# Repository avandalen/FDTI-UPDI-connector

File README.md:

# Small ATtiny self-clamping program connector
See the full article: https://www.avdweb.nl/arduino/attiny3217/ftdi-updi-connector
Typically, debugging via the serial monitor and burning the bootloader requires 2 connectors:  FTDI and UPDI (like the ICSP connector for the Atmega328 and others) These connectors, however, take up a lot of space on the pcb, especially with respect to the fact that the ATtiny devices, such as the ATtiny3217, are very small. That is why I have designed a new combined FTDI / UPDI connector, which take less space on the pcb.

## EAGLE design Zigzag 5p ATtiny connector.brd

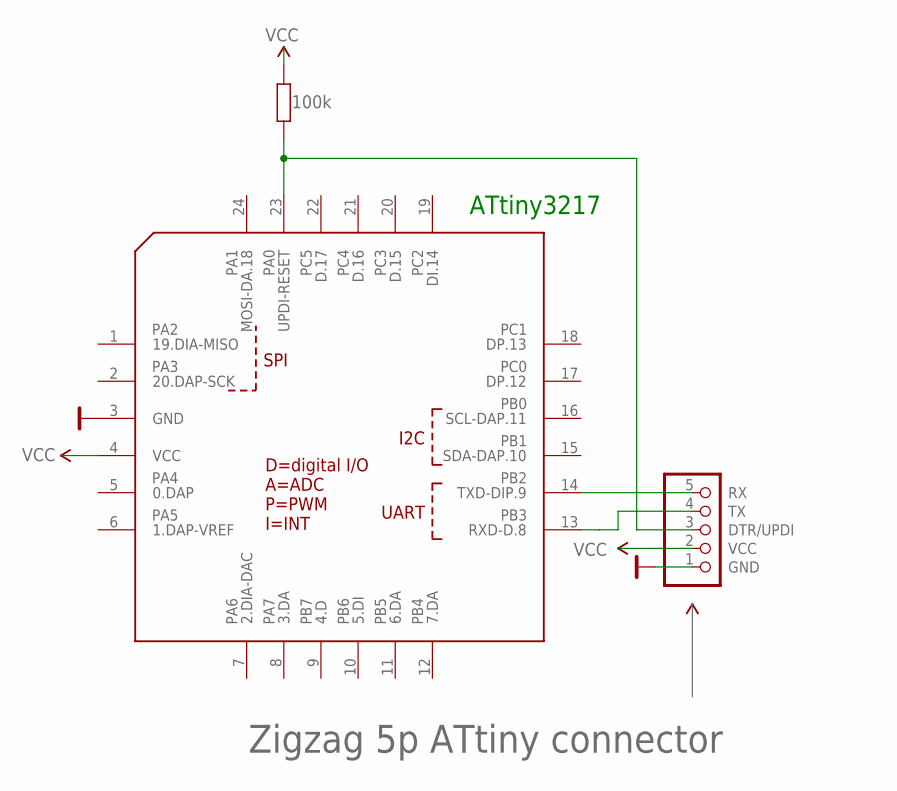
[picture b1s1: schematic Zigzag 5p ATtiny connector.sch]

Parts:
J1: 5 pin 0.05" ZIGZAG connector; ZIGZAG-FTDI-UPDI-5P
R1: 100k; 0603
U2: ATtiny3217; QFN-24

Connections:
DTR/UPDI: J1.3 (DTR/UPDI), R1.1, U2.23 (UPDI-RESET)
GND: J1.1 (GND), U2.3 (GND)
unnamed: J1.5 (RX), U2.14 (TXD-DIP.9)
unnamed: J1.4 (TX), U2.13 (RXD-D.8)
VCC: J1.2 (VCC), R1.2, U2.4 (VCC)

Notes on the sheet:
Zigzag 5p ATtiny connector
ATtiny3217

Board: 2 copper layers, 3 parts (0 on the bottom side), 5 nets, no tracks yet.

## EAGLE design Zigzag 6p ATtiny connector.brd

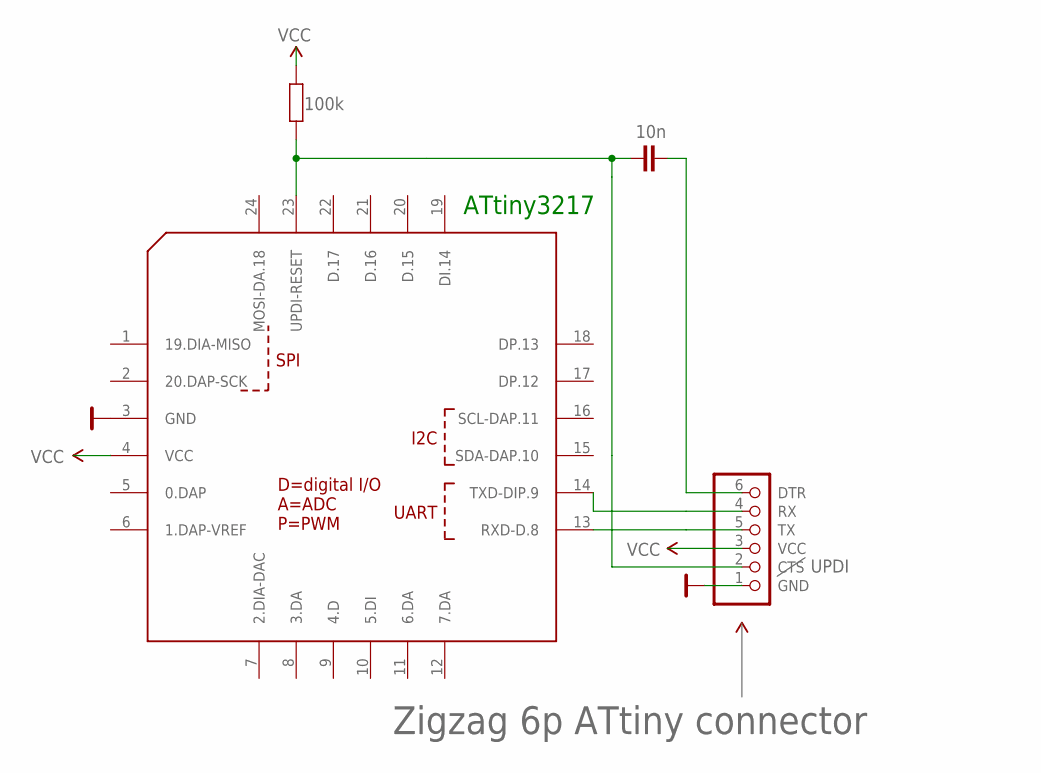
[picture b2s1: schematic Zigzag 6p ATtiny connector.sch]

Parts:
C2: 10n; 0603-SMALL
J2: FTDI; ZIGZAG-FTDI
R2: 100k; 0603-SMALL
U1: ATTINY3217-; QFN-24

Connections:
GND: J2.1 (GND), U1.3 (GND)
unnamed: C2.2, J2.6 (DTR)
unnamed: J2.4 (RX), U1.14 (TXD-DIP.9)
unnamed: J2.5 (TX), U1.13 (RXD-D.8)
UPDI: C2.1, J2.2 (CTS), R2.1, U1.23 (UPDI-RESET)
VCC: J2.3 (VCC), R2.2, U1.4 (VCC)

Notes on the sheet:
Zigzag 6p ATtiny connector
ATtiny3217

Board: 2 copper layers, 4 parts (0 on the bottom side), 6 nets, no tracks yet.

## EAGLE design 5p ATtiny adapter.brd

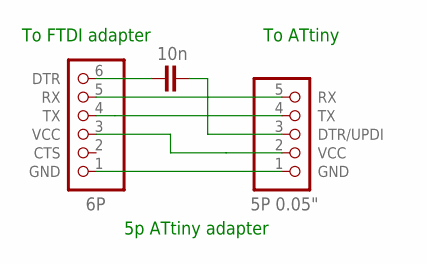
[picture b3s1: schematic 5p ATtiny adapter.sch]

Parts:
C1: 10n; 0603-SMALL
J1: 6P; 1X06
J2: 5P 0.05"; FTDI-UPDI-5P

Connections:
5V: J1.3 (VCC), J2.2 (VCC)
GND: J1.1 (GND), J2.1 (GND)
unnamed: C1.2, J2.3 (DTR/UPDI)
unnamed: C1.1, J1.6 (DTR)
unnamed: J1.5 (RX), J2.5 (RX)
unnamed: J1.4 (TX), J2.4 (TX)

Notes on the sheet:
5p ATtiny adapter
To FTDI adapter
To ATtiny

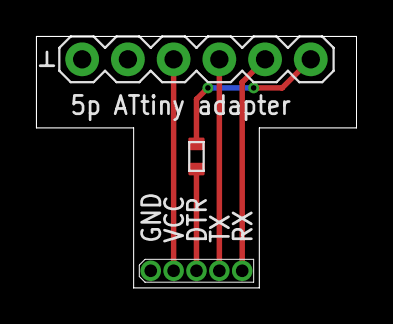
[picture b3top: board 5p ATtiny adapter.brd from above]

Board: 2 copper layers, 17.8 x 14.0 mm, 3 parts (0 on the bottom side), 6 nets.

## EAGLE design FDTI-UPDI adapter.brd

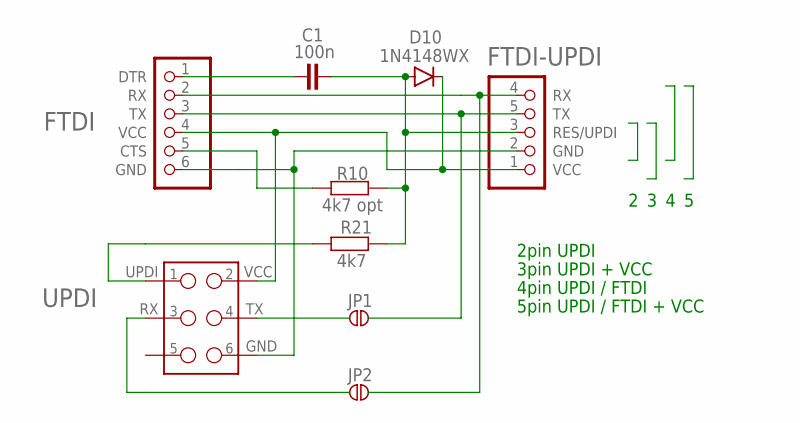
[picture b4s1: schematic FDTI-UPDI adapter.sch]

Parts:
C1: 100n; 0603-SMALL
D10: 1N4148WX; SOD-323
J2: FTDI; ZIGZAG-FTDI
J100: FTDI-UPDI; FTDI-UPDI-ZIGZAG
JP1, JP2: JUMPER_SJSMALL; SJ_2S-NO-NS
R10: 4k7 opt; 0603-SMALL
R21: 4k7; 0603-SMALL
UPDI: M3X2"; 2X3_TEST_POINTS

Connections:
4555: C1.2, D10.A, J100.3 (RES/UPDI), R10.1, R21.1
DTR1: C1.1, J2.1 (DTR)
GND: J2.6 (GND), J100.2 (GND), UPDI.6
unnamed: J2.5 (CTS), R10.2
RX: JP2.2, UPDI.3
RX1: J2.2 (RX), J100.4 (RX), JP2.1
TX: JP1.2, UPDI.4
TX1: J2.3 (TX), J100.5 (TX), JP1.1
UPDI: R21.2, UPDI.1
VCC: D10.C, J2.4 (VCC), J100.1 (VCC), UPDI.2

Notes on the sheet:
2pin UPDI
3pin UPDI + VCC
4pin UPDI / FTDI
5pin UPDI / FTDI + VCC

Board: 2 copper layers, 9 parts (0 on the bottom side), 10 nets, no tracks yet.

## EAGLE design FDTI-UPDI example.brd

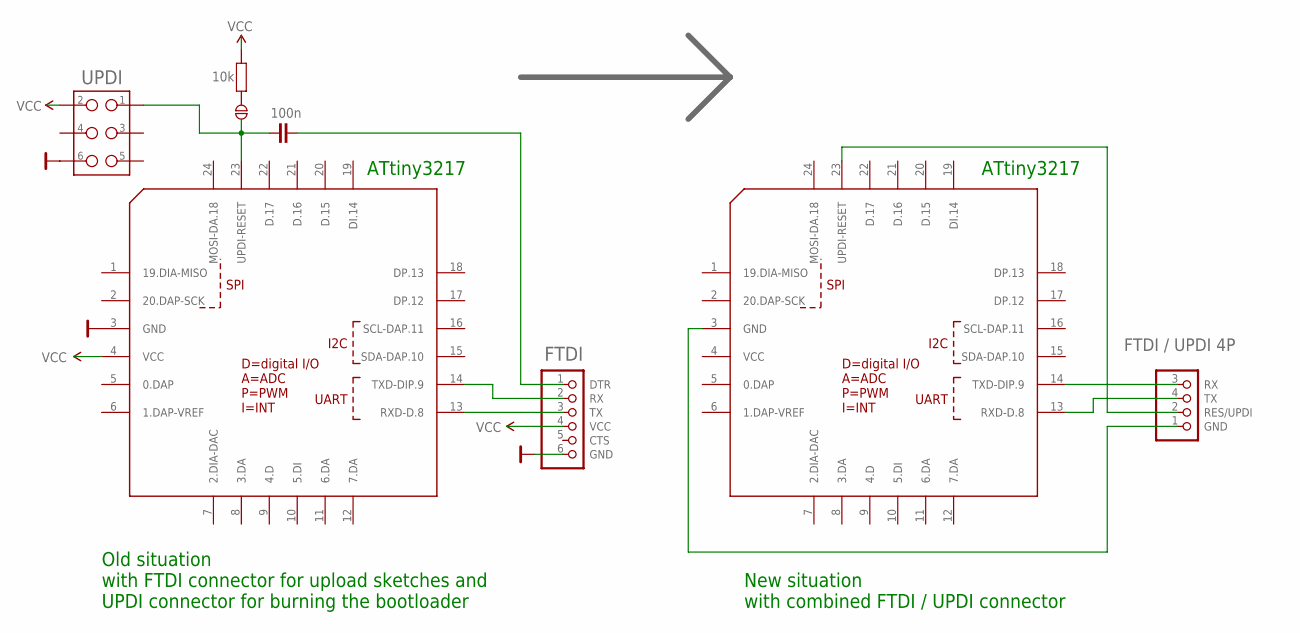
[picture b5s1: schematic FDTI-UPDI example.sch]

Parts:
C2: 100n; 0603-SMALL
J1: FTDI / UPDI 4P; ZIGZAG-FTDI-UPDI-4P
J2: FTDI; ZIGZAG-FTDI
JP1: JUMPER_SJSMALL; SJ_2S-NO-NS
R2: 10k; 0603-SMALL
U1: ATTINY3217-; QFN-24
U2: ATtiny3217; QFN-24
UPDI: M3X2"; 2X3_TEST_POINTS

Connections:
GND: J2.6 (GND), U1.3 (GND), UPDI.6
unnamed: J1.3 (RX), U2.14 (TXD-DIP.9)
unnamed: J1.4 (TX), U2.13 (RXD-D.8)
unnamed: J1.2 (RES/UPDI), U2.23 (UPDI-RESET)
unnamed: J1.1 (GND), U2.3 (GND)
unnamed: C2.1, JP1.1, U1.23 (UPDI-RESET), UPDI.1
unnamed: C2.2, J2.1 (DTR)
unnamed: J2.2 (RX), U1.14 (TXD-DIP.9)
unnamed: J2.3 (TX), U1.13 (RXD-D.8)
unnamed: JP1.2, R2.1
VCC: J2.4 (VCC), U1.4 (VCC), UPDI.2

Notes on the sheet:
Old situation with FTDI connector for upload sketches and UPDI connector for burning the bootloader
New situation with combined FTDI / UPDI connector
ATtiny3217

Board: 2 copper layers, 8 parts (0 on the bottom side), 11 nets, no tracks yet.

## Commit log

2021-05-24 Create LICENSE
